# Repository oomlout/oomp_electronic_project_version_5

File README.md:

# OOMP Electronic Projects

**Explore a board, understand its components, and follow it through to manufacturing files.**

This repository brings electronic board projects into a consistent, browsable
collection. Each project keeps its source files, component records, drawings,
and review results together, with interactive explorers and production outputs
where available. Matched parts link back to the
[OOMP Electronics catalogue](https://github.com/oomlout/oomp_electronic_version_5).

**[Browse projects](navigation/README.md)** · **[Board explorer guide](kicad_agents/BOARD_EXPLORER_GUIDE.md)** · **[Add a project](ADDING_PROJECTS.md)** · **[Component catalogue](https://github.com/oomlout/oomp_electronic_version_5)**

[![Component-placement drawing of the Adafruit PWM Servo Shield][board-image]][example]

*Example: [Adafruit PWM Servo Shield][example]. Browse its saved project record
or [open the interactive board explorer][explorer].*

## Find what you need

| I want to… | Start here |
| --- | --- |
| Browse boards and saved versions | [Project catalogue](navigation/README.md) |
| Inspect components, pins, and routed nets | [Board explorer guide](kicad_agents/BOARD_EXPLORER_GUIDE.md) |
| Add another board | [Adding projects](ADDING_PROJECTS.md) and [definition format](project_data/README.md) |
| Understand the converted KiCad design | [Conversion and library guide](kicad_agents/KICAD_LIBRARY_GUIDE.md) |
| Review fabrication and assembly outputs | [Production guide](kicad_agents/PRODUCTION_JLC_GUIDE.md) |
| See where an OOMP component is used | [Component usage](https://oomlout.github.io/oomp_electronic_project_version_5/usage/index.html) |

## What a project contains

- **Saved source files and provenance**, including the upstream board and Git reference.
- **Component matching** against a local OOMP catalogue, with unresolved matches
  and review decisions kept visible.
- **Board drawings and interactive explorers**, plus InteractiveHtmlBom where generated.
- **A separate OOMP KiCad design**, conversion reports, and project-local libraries.
- **Manufacturing outputs where generated**, including Gerbers, assembly files,
  and validation reports for review.

Each project lives in `parts/<project-id>/`. Its page links to the available
files and reports. Custom or modified board items are preserved when they cannot
be replaced with verified library assets.

## Set up a local checkout

Use **Python 3.12 or later**. On Windows, enable Git's long-path support when cloning:

```powershell
git clone -c core.longpaths=true https://github.com/oomlout/oomp_electronic_project_version_5.git C:\gh\oomp_electronic_project_version_5
cd C:\gh\oomp_electronic_project_version_5
py -3.12 -m venv .venv
.\.venv\Scripts\python.exe -m pip install -r requirements.txt
.\.venv\Scripts\Activate.ps1
python action_doctor.py
```

Choose another destination if needed. For an existing checkout, run
`git config core.longpaths true` once. The doctor command reports prerequisites
without changing the checkout.

| Tool | Used for |
| --- | --- |
| KiCad CLI and libraries | Conversion and production output |
| KiCad's Python with `pcbnew` | InteractiveHtmlBom |
| Inkscape | PNG rendering |
| Git | Explicit upstream-source refreshes |

KiCad 10 supports Eagle PCB import, but its CLI does not import an Eagle
schematic/project pair. The existing paired-source refresh path requires a CLI
providing `kicad-cli import`; otherwise it fails explicitly. Use KiCad's
**File → Import Non-KiCad Project** for paired Eagle conversion, then save native
inputs. The migrated native KiCad inputs build without refreshing Eagle sources.

The committed `component_catalog` snapshot supplies component metadata and
assets. Ordinary builds do not access an electronics checkout.
Its compiled matching index contains the same IDs and explicit generic rules as
the saved component records, avoiding thousands of metadata reads per board.

## Build a selected project

Copy its ID from a project page. For example:

```powershell
$projectId = 'oomp_project_github_hanqaqa_easyduino_esp32_current'
python action_generate.py --filter $projectId
```

To explicitly fetch upstream changes and run the production, image, and
interactive BOM stages:

```powershell
python action_generate.py --filter $projectId --refresh-sources --production --images --ibom
```

Normal generation uses saved project inputs. Source refresh is explicit, so a
documentation rebuild cannot silently fetch a different upstream board.
`--regenerate-pngs` replaces preserved PNGs. Missing tools, missing inputs and
failed stages must be resolved before claiming a complete build.

| Task | Command |
| --- | --- |
| Populate definitions without building projects | `python action_generate.py --populate-only` |
| Refresh the component-usage pages | `python action_generate_usage.py` |
| Run the project test suite | `python -m pytest` |
| Check independence from sibling repositories | `python -S tools/run_isolated_tests.py -q` |

### Add a board

Edit `project_data/<owner>/working.yaml`; follow the
[worked example](ADDING_PROJECTS.md) and [definition guide](project_data/README.md).
Project IDs and existing
`parts/<project-id>` paths remain stable. Project records under `parts_source`
are derived from these definitions.
Historical records no longer present in the active definitions remain selectable
by their existing ID and are marked `definition_source: preserved_working_record`.
Their saved Git reference, inputs and review decisions are retained.

## Update the component snapshot

```powershell
python action_sync_component_catalog.py --source C:\gh\oomp_electronic_version_5
```

The default source is configured in [`project_config.json`](project_config.json)
and can point to a different location. It is used only by
the explicit sync command. Updates are copied and checksum-verified in staging,
then installed as a complete snapshot. A previous snapshot is retained at
`component_catalog.previous`; archive it before another update. Inspect the
snapshot manifest and matching changes before committing an update.

Snapshot hashes describe actual imported files. The source commit is recorded
for provenance; local source modifications are not represented by that commit.
Missing component assets are listed explicitly in the manifest.

## Links and publishing

Public repository and Pages addresses are configured in `project_config.json`.
Projects link to canonical component pages. `usage/index.html#<oomp-id>` shows
confirmed project usage and reports incomplete extraction coverage. It also
handles unknown component IDs without requiring a per-component page.

The Pages workflow publishes self-contained board explorers, interactive BOMs and usage pages.
CAD sources, drawings, manufacturing outputs and other downloads are linked from
GitHub. `tools/package_pages.py` checks the publication size before deployment.
Repository settings must use GitHub Actions as the Pages publishing source.

## IC naming

IC component IDs in the frozen catalogue use
`electronic_ic_<function>_<subtype>_<package>_<manufacturer>_<mpn>`.
Function, subtype, and package occupy taxonomy levels **3, 4, and 5**; levels
6–13 are empty and manufacturer/MPN remain at **14/15**. The package is the last
regular taxonomy field. Local `component_taxonomy.package_token` keeps matching
and display code independent of the electronics checkout.

See the [electronics intake guide](https://github.com/oomlout/oomp_electronic_version_5/blob/main/kicad_agents/JLC_PART_INTAKE_AGENT.md)
for adding components under this convention.

## Maintainer reference

[Project tooling](kicad_agents/README.md) · [Adding projects](ADDING_PROJECTS.md) · [Project definitions](project_data/README.md)

<details>
<summary>Repository split and migration history</summary>

### Repository split — 14 November 2026

The split preserved 915 saved projects and imported a dependency snapshot of
2,966 components. Existing drawings, explorers, manufacturing files and review
decisions were moved; no bulk documentation or board regeneration was performed.
Saved reverse usage was relocated without recomputing matches. Twelve projects
were marked as lacking extracted data.

At the split, the isolated project suite passed 92 tests, including native KiCad
conversion and fabrication checks. Four pre-existing assertions remained: the historical
Bus Pirate J302 rotation, IC1 being unmatched despite its saved confirmed match,
an old render zoom, and an old Bus Pirate version expectation. These failures
were checked against the original code/data and retained for separate repair;
the migration does not change board geometry to satisfy them.

### IC naming — 15 November 2026

The catalogue migration moved IC packages after their functional taxonomy and
recomputed MD5/base36/BIP39 codes from canonical IDs. The snapshot manifest
retains its original provenance and records the migration.

</details>

[example]: parts/oomp_project_github_adafruit_adafruit_16_channel_pwm_servo_shield_adafruit_pwm_servo_shield_current/README.md
[board-image]: parts/oomp_project_github_adafruit_adafruit_16_channel_pwm_servo_shield_adafruit_pwm_servo_shield_current/data/generated_data/src/board_300.png
[explorer]: https://oomlout.github.io/oomp_electronic_project_version_5/parts/oomp_project_github_adafruit_adafruit_16_channel_pwm_servo_shield_adafruit_pwm_servo_shield_current/board_explorer.html

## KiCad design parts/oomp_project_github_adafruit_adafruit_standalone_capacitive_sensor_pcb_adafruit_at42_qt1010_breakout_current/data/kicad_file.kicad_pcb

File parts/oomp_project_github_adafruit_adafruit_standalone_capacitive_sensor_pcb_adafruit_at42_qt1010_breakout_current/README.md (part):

# Project adafruit/Adafruit-Standalone-Capacitive-Sensor-PCB Adafruit AT42 QT1010 Breakout current

[View the project on GitHub](https://github.com/adafruit/Adafruit-Standalone-Capacitive-Sensor-PCB/blob/master/Adafruit%20AT42QT1010%20Breakout.brd)

[Open the interactive board explorer (GitHub Pages)](https://oomlout.github.io/oomp_electronic_project_version_5/parts/oomp_project_github_adafruit_adafruit_standalone_capacitive_sensor_pcb_adafruit_at42_qt1010_breakout_current/board_explorer.html)

[Browse this project category](../../navigation/oomp/project/github/adafruit/adafruit_standalone_capacitive_sensor_pcb/adafruit_at42_qt1010_breakout/README.md)

Project adafruit/Adafruit-Standalone-Capacitive-Sensor-PCB Adafruit AT42 QT1010 Breakout current is a KiCad project containing 26 extracted component records. The catalogue matcher linked 9 physical placements to OOMP parts.

## Project snapshot

| Item | Count |
| --- | ---: |
| Components | 26 |
| PCB footprints | 17 |
| Mounting and locating holes | 5 |
| Matched OOMP mounting-hole items | 5 |
| Schematic symbols | 25 |
| Matched OOMP components | 9 |
| Unmatched physical components | 3 |
| Front-side placements | 7 |
| Back-side placements | 1 |
| Project version | `current` |
| Git ref | `master` |

## Board

[Original KiCad files](https://github.com/oomlout/oomp_electronic_project_version_5/tree/main/parts/oomp_project_github_adafruit_adafruit_standalone_capacitive_sensor_pcb_adafruit_at42_qt1010_breakout_current/data/original) · [OOMP KiCad design and local libraries](https://github.com/oomlout/oomp_electronic_project_version_5/tree/main/parts/oomp_project_github_adafruit_adafruit_standalone_capacitive_sensor_pcb_adafruit_at42_qt1010_breakout_current/data/oomp_design) · [Conversion / skipped-item report](https://github.com/oomlout/oomp_electronic_project_version_5/blob/main/parts/oomp_project_github_adafruit_adafruit_standalone_capacitive_sensor_pcb_adafruit_at42_qt1010_breakout_current/data/oomp_design/conversion_report.yaml)

The OOMP design is a separate copy. Only symbols and footprints verified against unchanged installed KiCad masters are replaced; custom and modified items are retained.

- Approximate size: **20.32 mm × 27.94 mm**
- Outline source: `KiCad Edge.Cuts`
- Placement drawing: [view `board.svg`](https://github.com/oomlout/oomp_electronic_project_version_5/blob/main/parts/oomp_project_github_adafruit_adafruit_standalone_capacitive_sensor_pcb_adafruit_at42_qt1010_breakout_current/data/generated_data/src/board.svg)
- PNG placement drawing: [view `board.png`](https://github.com/oomlout/oomp_electronic_project_version_5/blob/main/parts/oomp_project_github_adafruit_adafruit_standalone_capacitive_sensor_pcb_adafruit_at42_qt1010_breakout_current/data/generated_data/src/board.png)
- 300-pixel placement preview: [view `board_300.png`](https://github.com/oomlout/oomp_electronic_project_version_5/blob/main/parts/oomp_project_github_adafruit_adafruit_standalone_capacitive_sensor_pcb_adafruit_at42_qt1010_breakout_current/data/generated_data/src/board_300.png)
- Placement drawing with pin names: [view `board_pins.svg`](https://github.com/oomlout/oomp_electronic_project_version_5/blob/main/parts/oomp_project_github_adafruit_adafruit_standalone_capacitive_sensor_pcb_adafruit_at42_qt1010_breakout_current/data/generated_data/src/board_pins.svg)
- PNG drawing with pin names: [view `board_pins.png`](https://github.com/oomlout/oomp_electronic_project_version_5/blob/main/parts/oomp_project_github_adafruit_adafruit_standalone_capacitive_sensor_pcb_adafruit_at42_qt1010_breakout_current/data/generated_data/src/board_pins.png)
- 300-pixel pin preview: [view `board_pins_300.png`](https://github.com/oomlout/oomp_electronic_project_version_5/blob/main/parts/oomp_project_github_adafruit_adafruit_standalone_capacitive_sensor_pcb_adafruit_at42_qt1010_breakout_current/data/generated_data/src/board_pins_300.png)
- Bottom placement drawing: [view `board_bottom.svg`](https://github.com/oomlout/oomp_electronic_project_version_5/blob/main/parts/oomp_project_github_adafruit_adafruit_standalone_capacitive_sensor_pcb_adafruit_at42_qt1010_breakout_current/data/generated_data/src/board_bottom.svg)
- Bottom PNG placement drawing: [view `board_bottom.png`](https://github.com/oomlout/oomp_electronic_project_version_5/blob/main/parts/oomp_project_github_adafruit_adafruit_standalone_capacitive_sensor_pcb_adafruit_at42_qt1010_breakout_current/data/generated_data/src/board_bottom.png)
- 300-pixel bottom preview: [view `board_bottom_300.png`](https://github.com/oomlout/oomp_electronic_project_version_5/blob/main/parts/oomp_project_github_adafruit_adafruit_standalone_capacitive_sensor_pcb_adafruit_at42_qt1010_breakout_current/data/generated_data/src/board_bottom_300.png)
- Bottom placement drawing with pin names: [view `board_pins_bottom.svg`](https://github.com/oomlout/oomp_electronic_project_version_5/blob/main/parts/oomp_project_github_adafruit_adafruit_standalone_capacitive_sensor_pcb_adafruit_at42_qt1010_breakout_current/data/generated_data/src/board_pins_bottom.svg)
- Bottom PNG drawing with pin names: [view `board_pins_bottom.png`](https://github.com/oomlout/oomp_electronic_project_version_5/blob/main/parts/oomp_project_github_adafruit_adafruit_standalone_capacitive_sensor_pcb_adafruit_at42_qt1010_breakout_current/data/generated_data/src/board_pins_bottom.png)
- 300-pixel bottom pin preview: [view `board_pins_bottom_300.png`](https://github.com/oomlout/oomp_electronic_project_version_5/blob/main/parts/oomp_project_github_adafruit_adafruit_standalone_capacitive_sensor_pcb_adafruit_at42_qt1010_breakout_current/data/generated_data/src/board_pins_bottom_300.png)
- Mechanical drawing: [view `board_mechanical.svg`](https://github.com/oomlout/oomp_electronic_project_version_5/blob/main/parts/oomp_project_github_adafruit_adafruit_standalone_capacitive_sensor_pcb_adafruit_at42_qt1010_breakout_current/data/generated_data/src/board_mechanical.svg)
- Mechanical PNG: [view `board_mechanical.png`](https://github.com/oomlout/oomp_electronic_project_version_5/blob/main/parts/oomp_project_github_adafruit_adafruit_standalone_capacitive_sensor_pcb_adafruit_at42_qt1010_breakout_current/data/generated_data/src/board_mechanical.png)
- 300-pixel mechanical preview: [view `board_mechanical_300.png`](https://github.com/oomlout/oomp_electronic_project_version_5/blob/main/parts/oomp_project_github_adafruit_adafruit_standalone_capacitive_sensor_pcb_adafruit_at42_qt1010_breakout_current/data/generated_data/src/board_mechanical_300.png)
- Open the board explorer on GitHub Pages: [explore this board](https://oomlout.github.io/oomp_electronic_project_version_5/parts/oomp_project_github_adafruit_adafruit_standalone_capacitive_sensor_pcb_adafruit_at42_qt1010_breakout_current/board_explorer.html)
- InteractiveHtmlBom generation is configured; install KiCad or set `KICAD_PYTHON` to its bundled Python to build `data/interactivehtmlbom/ibom.html`.

## Board with pins

## Bottom board with pins

The bottom view is mirrored horizontally so it is shown as viewed from beneath the assembled board.

## Mechanical layer

The table uses a board-relative origin at the minimum X/Y point of `Edge.Cuts`. This point is shown as **0,0** in the mechanical drawing; X increases right and Y increases down. Original KiCad coordinates are retained alongside it.

### Diameter 2.5 mm holes

| OOMP reference | Source | Name | Classification | Role | Board X (mm) | Board Y (mm) | OOMP part |
| --- | --- | --- | --- | --- | ---: | ---: | --- |
| `MH1` | `LED1` | Mounting Hole 2.5 mm Round Unplated | `mechanical / mounting_hole / 2_5_mm / round / unplated` | locating | 10.230 | 2.183 | [`mechanical_mounting_hole_2_5_mm_round_unplated`](https://github.com/oomlout/oomp_electronic_version_5/tree/main/parts/mechanical_mounting_hole_2_5_mm_round_unplated) |
| `MH2` | `U$6` | Mounting Hole 2.5 mm Round Plated | `mechanical / mounting_hole / 2_5_mm / round / plated` | mounting | 17.780 | 25.400 | [`mechanical_mounting_hole_2_5_mm_round_plated`](https://github.com/oomlout/oomp_electronic_version_5/tree/main/parts/mechanical_mounting_hole_2_5_mm_round_plated) |
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
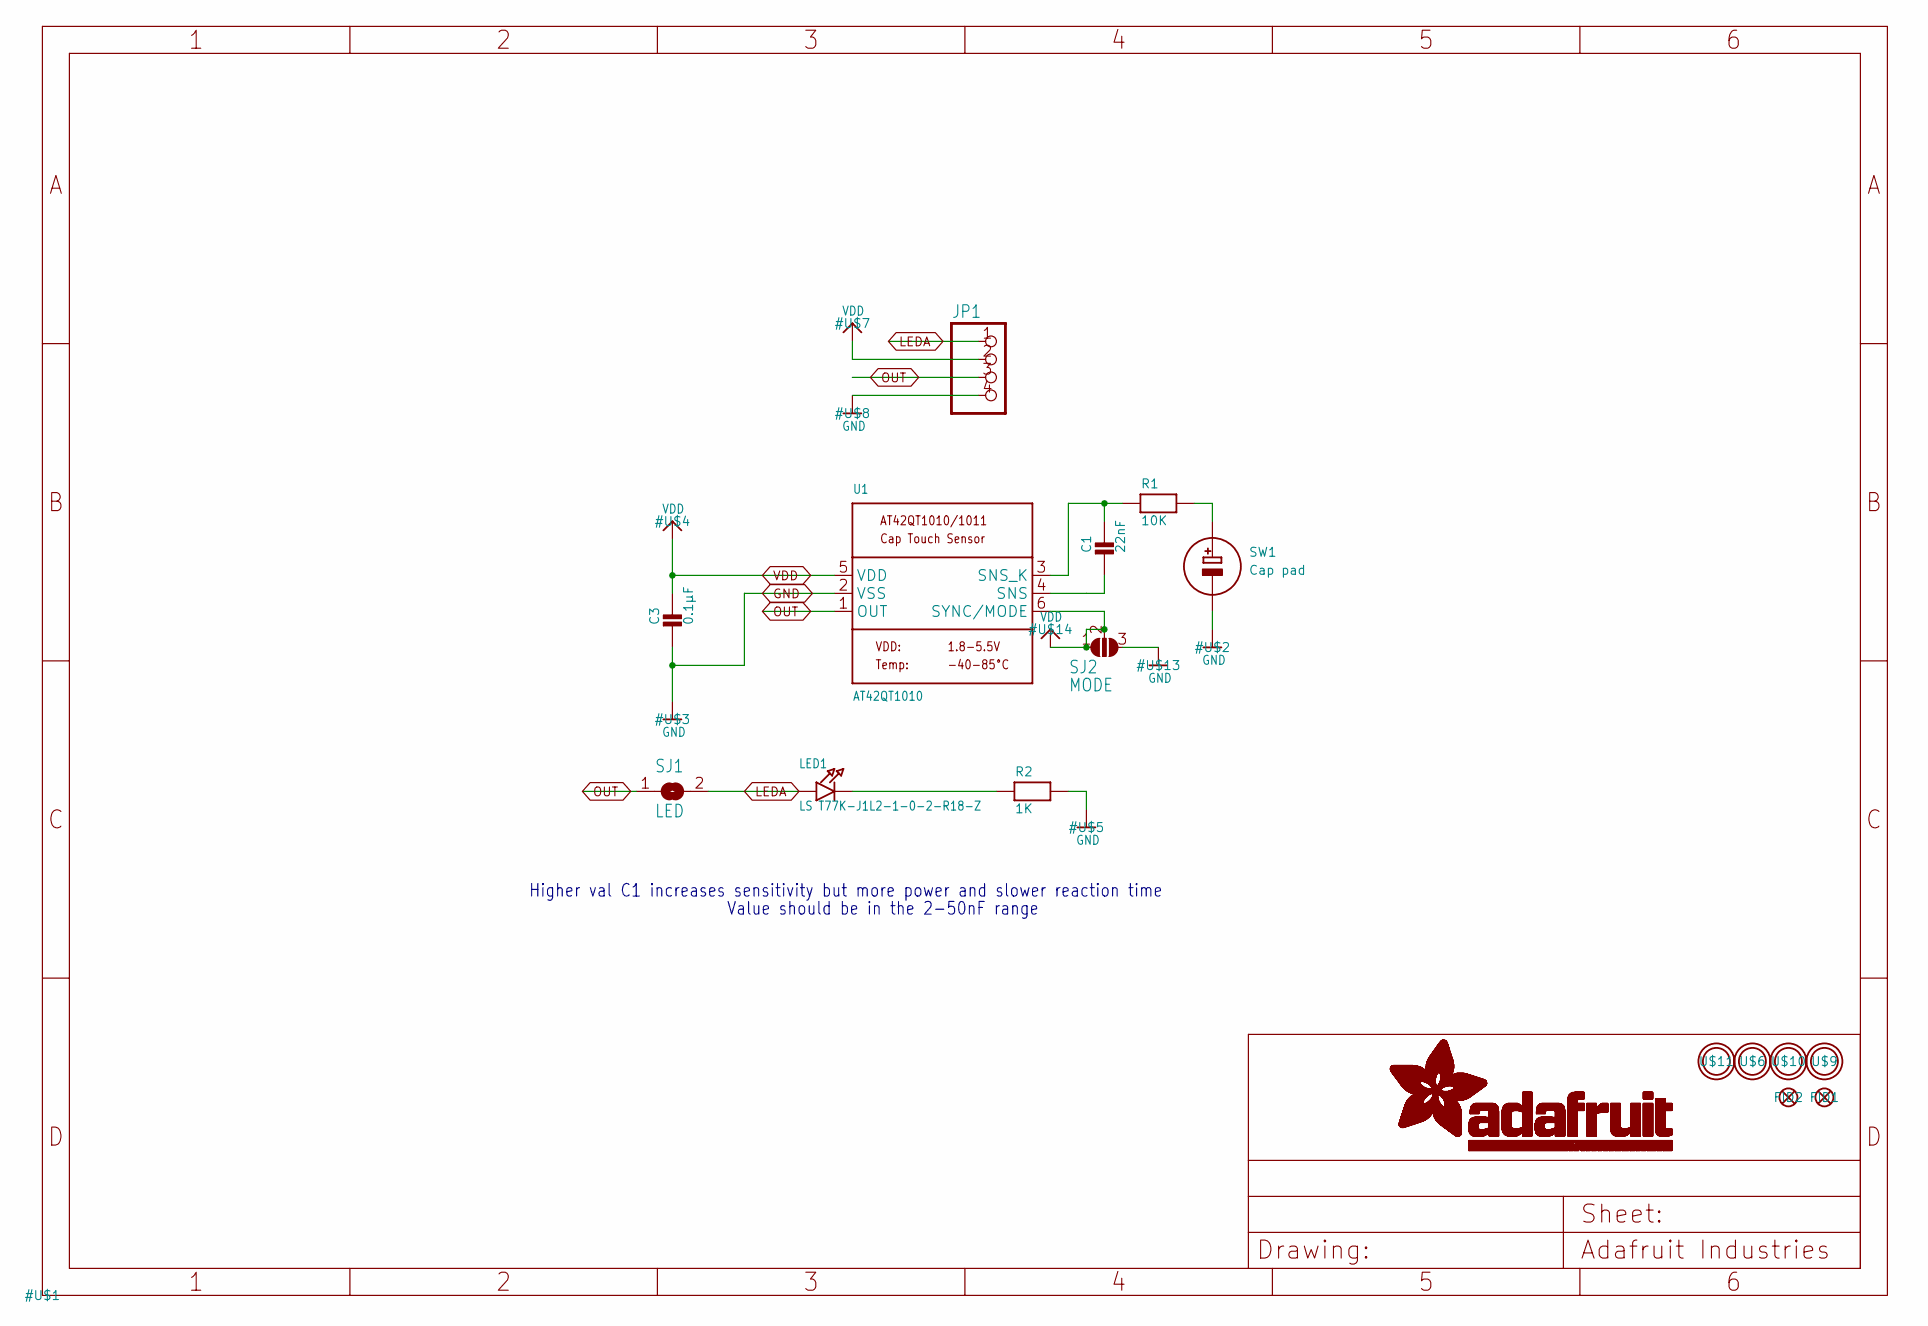
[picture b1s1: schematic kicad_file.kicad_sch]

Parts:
C1: 22nF; _0805
C3: 0.1µF; _0805
FID1, FID2: FIDUCIAL""; FIDUCIAL_1MM
JP1: HEADER-1X476MIL; 1X04_ROUND_76
LED1: LS T77K-J1L2-1-0-2-R18-Z; PLCC2_REVMOUNT
R1: 10K; _0805
R2: 1K; _0805
SJ1: LED; SOLDERJUMPER_CLOSEDWIRE
SJ2: MODE; SOLDERJUMPER_2WAY_OPEN_NOPASTE
SW1: Cap pad; CAPTOUCH_SIMPLE_12.5MM
U1: AT42QT1010; SOT23-6
U$6, U$9, U$10, U$11: MOUNTINGHOLE2.5; MOUNTINGHOLE_2.5_PLATED

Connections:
CAPPAD: R1.2, SW1.E (+)
GND: C3.2, JP1.4, R2.2, SJ2.3, SW1.G (-), U1.2 (VSS)
LEDA: JP1.1, LED1.A, SJ1.2
unnamed: C1.2, U1.4 (SNS)
unnamed: C1.1, R1.1, U1.3 (SNS_K)
unnamed: LED1.K (C), R2.1
OUT: JP1.3, SJ1.1, U1.1 (OUT)
VDD: C3.1, JP1.2, SJ2.1, SJ2.2, U1.5 (VDD), U1.6 (SYNC/MODE)

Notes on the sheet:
Value should be in the 2-50nF range
Higher val C1 increases sensitivity but more power and slower reaction time

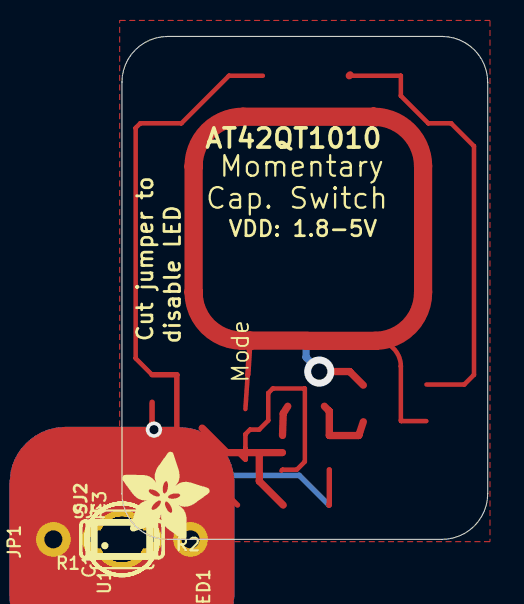
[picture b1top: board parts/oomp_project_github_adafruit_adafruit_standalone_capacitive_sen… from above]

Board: 2 copper layers, 20.3 x 27.9 mm, 17 parts (1 on the bottom side), 8 nets.

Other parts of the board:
U$12: ADAFRUIT_5MM

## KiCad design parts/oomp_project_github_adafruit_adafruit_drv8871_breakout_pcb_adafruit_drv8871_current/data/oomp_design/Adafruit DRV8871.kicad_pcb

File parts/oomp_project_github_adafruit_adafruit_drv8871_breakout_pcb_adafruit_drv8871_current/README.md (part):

# Project adafruit/Adafruit-DRV8871-Breakout-PCB Adafruit DRV8871 current

[View the project on GitHub](https://github.com/adafruit/Adafruit-DRV8871-Breakout-PCB/blob/master/Adafruit%20DRV8871.brd)

[Open the interactive board explorer (GitHub Pages)](https://oomlout.github.io/oomp_electronic_project_version_5/parts/oomp_project_github_adafruit_adafruit_drv8871_breakout_pcb_adafruit_drv8871_current/board_explorer.html)

[Browse this project category](../../navigation/oomp/project/github/adafruit/adafruit_drv8871_breakout_pcb/adafruit_drv8871/README.md)

Project adafruit/Adafruit-DRV8871-Breakout-PCB Adafruit DRV8871 current is a KiCad project containing 26 extracted component records. The catalogue matcher linked 5 physical placements to OOMP parts.

## Project snapshot

| Item | Count |
| --- | ---: |
| Components | 26 |
| PCB footprints | 15 |
| Mounting and locating holes | 6 |
| Matched OOMP mounting-hole items | 2 |
| Schematic symbols | 23 |
| Matched OOMP components | 5 |
| Unmatched physical components | 4 |
| Front-side placements | 7 |
| Back-side placements | 0 |
| Project version | `current` |
| Git ref | `master` |

## Board

[Original KiCad files](https://github.com/oomlout/oomp_electronic_project_version_5/tree/main/parts/oomp_project_github_adafruit_adafruit_drv8871_breakout_pcb_adafruit_drv8871_current/data/original) · [OOMP KiCad design and local libraries](https://github.com/oomlout/oomp_electronic_project_version_5/tree/main/parts/oomp_project_github_adafruit_adafruit_drv8871_breakout_pcb_adafruit_drv8871_current/data/oomp_design) · [Conversion / skipped-item report](https://github.com/oomlout/oomp_electronic_project_version_5/blob/main/parts/oomp_project_github_adafruit_adafruit_drv8871_breakout_pcb_adafruit_drv8871_current/data/oomp_design/conversion_report.yaml)

The OOMP design is a separate copy. Only symbols and footprints verified against unchanged installed KiCad masters are replaced; custom and modified items are retained.

- Approximate size: **20.32 mm × 24.13 mm**
- Outline source: `KiCad Edge.Cuts`
- Placement drawing: [view `board.svg`](https://github.com/oomlout/oomp_electronic_project_version_5/blob/main/parts/oomp_project_github_adafruit_adafruit_drv8871_breakout_pcb_adafruit_drv8871_current/data/generated_data/src/board.svg)
- PNG placement drawing: [view `board.png`](https://github.com/oomlout/oomp_electronic_project_version_5/blob/main/parts/oomp_project_github_adafruit_adafruit_drv8871_breakout_pcb_adafruit_drv8871_current/data/generated_data/src/board.png)
- 300-pixel placement preview: [view `board_300.png`](https://github.com/oomlout/oomp_electronic_project_version_5/blob/main/parts/oomp_project_github_adafruit_adafruit_drv8871_breakout_pcb_adafruit_drv8871_current/data/generated_data/src/board_300.png)
- Placement drawing with pin names: [view `board_pins.svg`](https://github.com/oomlout/oomp_electronic_project_version_5/blob/main/parts/oomp_project_github_adafruit_adafruit_drv8871_breakout_pcb_adafruit_drv8871_current/data/generated_data/src/board_pins.svg)
- PNG drawing with pin names: [view `board_pins.png`](https://github.com/oomlout/oomp_electronic_project_version_5/blob/main/parts/oomp_project_github_adafruit_adafruit_drv8871_breakout_pcb_adafruit_drv8871_current/data/generated_data/src/board_pins.png)
- 300-pixel pin preview: [view `board_pins_300.png`](https://github.com/oomlout/oomp_electronic_project_version_5/blob/main/parts/oomp_project_github_adafruit_adafruit_drv8871_breakout_pcb_adafruit_drv8871_current/data/generated_data/src/board_pins_300.png)
- Bottom placement drawing: [view `board_bottom.svg`](https://github.com/oomlout/oomp_electronic_project_version_5/blob/main/parts/oomp_project_github_adafruit_adafruit_drv8871_breakout_pcb_adafruit_drv8871_current/data/generated_data/src/board_bottom.svg)
- Bottom PNG placement drawing: [view `board_bottom.png`](https://github.com/oomlout/oomp_electronic_project_version_5/blob/main/parts/oomp_project_github_adafruit_adafruit_drv8871_breakout_pcb_adafruit_drv8871_current/data/generated_data/src/board_bottom.png)
- 300-pixel bottom preview: [view `board_bottom_300.png`](https://github.com/oomlout/oomp_electronic_project_version_5/blob/main/parts/oomp_project_github_adafruit_adafruit_drv8871_breakout_pcb_adafruit_drv8871_current/data/generated_data/src/board_bottom_300.png)
- Bottom placement drawing with pin names: [view `board_pins_bottom.svg`](https://github.com/oomlout/oomp_electronic_project_version_5/blob/main/parts/oomp_project_github_adafruit_adafruit_drv8871_breakout_pcb_adafruit_drv8871_current/data/generated_data/src/board_pins_bottom.svg)
- Bottom PNG drawing with pin names: [view `board_pins_bottom.png`](https://github.com/oomlout/oomp_electronic_project_version_5/blob/main/parts/oomp_project_github_adafruit_adafruit_drv8871_breakout_pcb_adafruit_drv8871_current/data/generated_data/src/board_pins_bottom.png)
- 300-pixel bottom pin preview: [view `board_pins_bottom_300.png`](https://github.com/oomlout/oomp_electronic_project_version_5/blob/main/parts/oomp_project_github_adafruit_adafruit_drv8871_breakout_pcb_adafruit_drv8871_current/data/generated_data/src/board_pins_bottom_300.png)
- Mechanical drawing: [view `board_mechanical.svg`](https://github.com/oomlout/oomp_electronic_project_version_5/blob/main/parts/oomp_project_github_adafruit_adafruit_drv8871_breakout_pcb_adafruit_drv8871_current/data/generated_data/src/board_mechanical.svg)
- Mechanical PNG: [view `board_mechanical.png`](https://github.com/oomlout/oomp_electronic_project_version_5/blob/main/parts/oomp_project_github_adafruit_adafruit_drv8871_breakout_pcb_adafruit_drv8871_current/data/generated_data/src/board_mechanical.png)
- 300-pixel mechanical preview: [view `board_mechanical_300.png`](https://github.com/oomlout/oomp_electronic_project_version_5/blob/main/parts/oomp_project_github_adafruit_adafruit_drv8871_breakout_pcb_adafruit_drv8871_current/data/generated_data/src/board_mechanical_300.png)
- Open the board explorer on GitHub Pages: [explore this board](https://oomlout.github.io/oomp_electronic_project_version_5/parts/oomp_project_github_adafruit_adafruit_drv8871_breakout_pcb_adafruit_drv8871_current/board_explorer.html)
- InteractiveHtmlBom generation is configured; install KiCad or set `KICAD_PYTHON` to its bundled Python to build `data/interactivehtmlbom/ibom.html`.

## Board with pins

## Bottom board with pins

The bottom view is mirrored horizontally so it is shown as viewed from beneath the assembled board.

## Mechanical layer

The table uses a board-relative origin at the minimum X/Y point of `Edge.Cuts`. This point is shown as **0,0** in the mechanical drawing; X increases right and Y increases down. Original KiCad coordinates are retained alongside it.

### Diameter 0.4 mm holes

| OOMP reference | Source | Name | Classification | Role | Board X (mm) | Board Y (mm) | OOMP part |
| --- | --- | --- | --- | --- | ---: | ---: | --- |
| `MH1` | `U1` | Mounting Hole 0.4 mm Round Plated | `` | shield_mount | 3.699 | 12.458 | unmatched (`mechanical_mounting_hole_0_4_mm_round_plated` proposed) |
| `MH2` | `U1` | Mounting Hole 0.4 mm Round Plated | `` | shield_mount | 3.699 | 13.958 | unmatched (`mechanical_mounting_hole_0_4_mm_round_plated` proposed) |
| `MH4` | `U1` | Mounting Hole 0.4 mm Round Plated | `` | shield_mount | 5.699 | 12.458 | unmatched (`mechanical_mounting_hole_0_4_mm_round_plated` proposed) |
| `MH3` | `U1` | Mounting Hole 0.4 mm Round Plated | `` | shield_mount | 5.699 | 13.958 | unmatched (`mechanical_mounting_hole_0_4_mm_round_plated` proposed) |

### Diameter 2.5 mm holes

| OOMP reference | Source | Name | Classification | Role | Board X (mm) | Board Y (mm) | OOMP part |
| --- | --- | --- | --- | --- | ---: | ---: | --- |
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
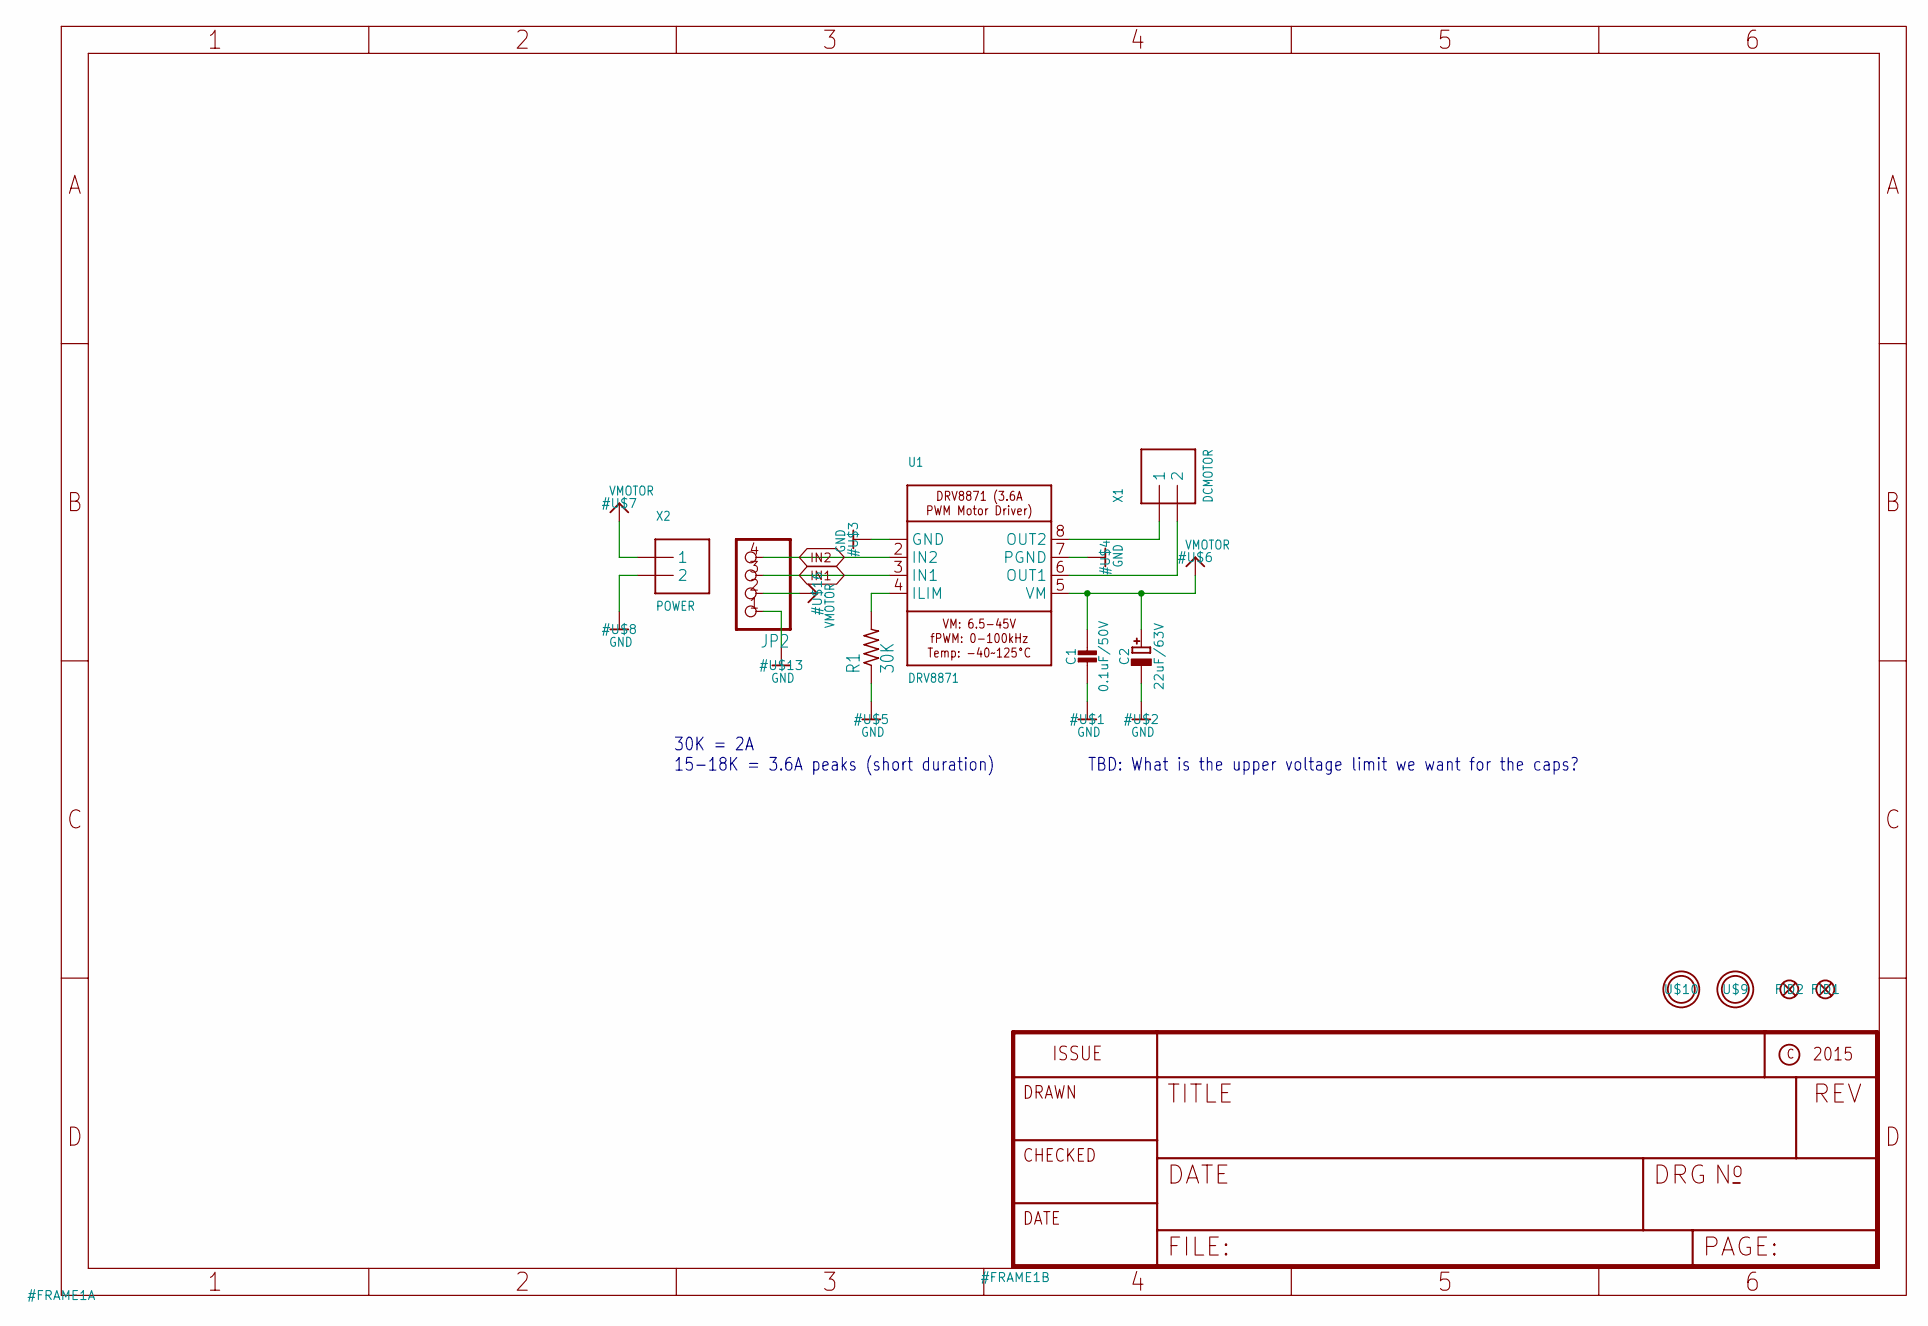
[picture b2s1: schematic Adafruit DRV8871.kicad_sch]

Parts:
C1: 0.1uF/50V; 0805-NO
C2: 22uF/63V; PANASONIC_D
FID1, FID2: FIDUCIAL""; FIDUCIAL_1MM
JP2: HEADER-1X476MIL; 1X04_ROUND_76
R1: 30K; 0805-THM
U1: DRV8871; HSOP8
U$9, U$10: MOUNTINGHOLE2.5; MOUNTINGHOLE_2.5_PLATED
X1: DCMOTOR; TERMBLOCK_1X2-3.5MM
X2: POWER; TERMBLOCK_1X2-3.5MM

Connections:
GND: C1.2, C2.-, JP2.1, R1.1, U1.1 (GND), U1.7 (PGND), U1.GND, U1.P$1 (GND), U1.P$2 (GND), U1.P$3 (GND), U1.P$4 (GND), X2.2
IN1: JP2.3, U1.3 (IN1)
IN2: JP2.4, U1.2 (IN2)
unnamed: R1.2, U1.4 (ILIM)
OUT1: U1.6 (OUT1), X1.2
OUT2: U1.8 (OUT2), X1.1
VMOTOR: C1.1, C2.+, JP2.2, U1.5 (VM), X2.1

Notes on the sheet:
30K = 2A 15-18K = 3.6A peaks (short duration~{})
TBD: What is the upper voltage limit we want for the caps?

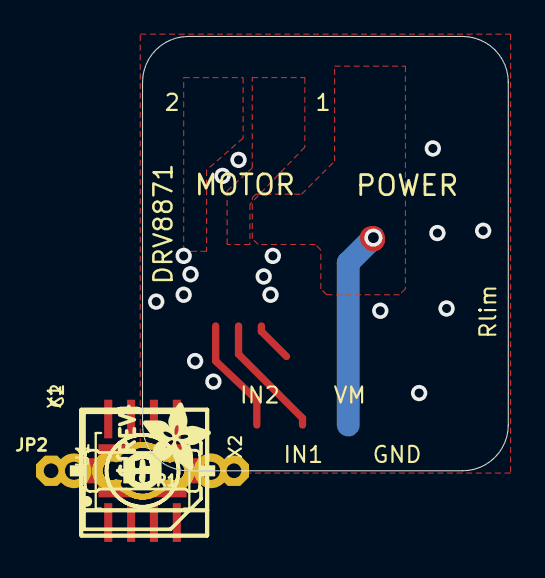
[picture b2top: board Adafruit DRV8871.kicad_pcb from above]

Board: 2 copper layers, 20.3 x 24.1 mm, 15 parts (0 on the bottom side), 7 nets.

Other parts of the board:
U$11: SYMBOL_PLUS
U$12: SYMBOL_MINUS
U$14: ADAFRUIT_3.5MM
U$15: PCBFEAT-REV-040

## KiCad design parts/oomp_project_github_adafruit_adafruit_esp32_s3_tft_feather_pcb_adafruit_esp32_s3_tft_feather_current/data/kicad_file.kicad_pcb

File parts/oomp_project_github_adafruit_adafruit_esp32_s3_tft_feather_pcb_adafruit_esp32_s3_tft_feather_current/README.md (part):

# Project adafruit/Adafruit-ESP32-S3-TFT-Feather-PCB Adafruit ESP32 S3 TFT Feather current

[View the project on GitHub](https://github.com/adafruit/Adafruit-ESP32-S3-TFT-Feather-PCB/blob/main/Adafruit%20ESP32-S3%20TFT%20Feather.brd)

[Open the interactive board explorer (GitHub Pages)](https://oomlout.github.io/oomp_electronic_project_version_5/parts/oomp_project_github_adafruit_adafruit_esp32_s3_tft_feather_pcb_adafruit_esp32_s3_tft_feather_current/board_explorer.html)

[Browse this project category](../../navigation/oomp/project/github/adafruit/adafruit_esp32_s3_tft_feather_pcb/adafruit_esp32_s3_tft_feather/README.md)

Project adafruit/Adafruit-ESP32-S3-TFT-Feather-PCB Adafruit ESP32 S3 TFT Feather current is a KiCad project containing 112 extracted component records. The catalogue matcher linked 32 physical placements to OOMP parts.

## Project snapshot

| Item | Count |
| --- | ---: |
| Components | 112 |
| PCB footprints | 56 |
| Mounting and locating holes | 8 |
| Matched OOMP mounting-hole items | 8 |
| Schematic symbols | 115 |
| Matched OOMP components | 32 |
| Unmatched physical components | 16 |
| Front-side placements | 33 |
| Back-side placements | 11 |
| Project version | `current` |
| Git ref | `main` |

## Board

[Original KiCad files](https://github.com/oomlout/oomp_electronic_project_version_5/tree/main/parts/oomp_project_github_adafruit_adafruit_esp32_s3_tft_feather_pcb_adafruit_esp32_s3_tft_feather_current/data/original) · [OOMP KiCad design and local libraries](https://github.com/oomlout/oomp_electronic_project_version_5/tree/main/parts/oomp_project_github_adafruit_adafruit_esp32_s3_tft_feather_pcb_adafruit_esp32_s3_tft_feather_current/data/oomp_design) · [Conversion / skipped-item report](https://github.com/oomlout/oomp_electronic_project_version_5/blob/main/parts/oomp_project_github_adafruit_adafruit_esp32_s3_tft_feather_pcb_adafruit_esp32_s3_tft_feather_current/data/oomp_design/conversion_report.yaml)

The OOMP design is a separate copy. Only symbols and footprints verified against unchanged installed KiCad masters are replaced; custom and modified items are retained.

- Approximate size: **50.8 mm × 22.86 mm**
- Outline source: `KiCad Edge.Cuts`
- Placement drawing: [view `board.svg`](https://github.com/oomlout/oomp_electronic_project_version_5/blob/main/parts/oomp_project_github_adafruit_adafruit_esp32_s3_tft_feather_pcb_adafruit_esp32_s3_tft_feather_current/data/generated_data/src/board.svg)
- PNG placement drawing: [view `board.png`](https://github.com/oomlout/oomp_electronic_project_version_5/blob/main/parts/oomp_project_github_adafruit_adafruit_esp32_s3_tft_feather_pcb_adafruit_esp32_s3_tft_feather_current/data/generated_data/src/board.png)
- 300-pixel placement preview: [view `board_300.png`](https://github.com/oomlout/oomp_electronic_project_version_5/blob/main/parts/oomp_project_github_adafruit_adafruit_esp32_s3_tft_feather_pcb_adafruit_esp32_s3_tft_feather_current/data/generated_data/src/board_300.png)
- Placement drawing with pin names: [view `board_pins.svg`](https://github.com/oomlout/oomp_electronic_project_version_5/blob/main/parts/oomp_project_github_adafruit_adafruit_esp32_s3_tft_feather_pcb_adafruit_esp32_s3_tft_feather_current/data/generated_data/src/board_pins.svg)
- PNG drawing with pin names: [view `board_pins.png`](https://github.com/oomlout/oomp_electronic_project_version_5/blob/main/parts/oomp_project_github_adafruit_adafruit_esp32_s3_tft_feather_pcb_adafruit_esp32_s3_tft_feather_current/data/generated_data/src/board_pins.png)
- 300-pixel pin preview: [view `board_pins_300.png`](https://github.com/oomlout/oomp_electronic_project_version_5/blob/main/parts/oomp_project_github_adafruit_adafruit_esp32_s3_tft_feather_pcb_adafruit_esp32_s3_tft_feather_current/data/generated_data/src/board_pins_300.png)
- Bottom placement drawing: [view `board_bottom.svg`](https://github.com/oomlout/oomp_electronic_project_version_5/blob/main/parts/oomp_project_github_adafruit_adafruit_esp32_s3_tft_feather_pcb_adafruit_esp32_s3_tft_feather_current/data/generated_data/src/board_bottom.svg)
- Bottom PNG placement drawing: [view `board_bottom.png`](https://github.com/oomlout/oomp_electronic_project_version_5/blob/main/parts/oomp_project_github_adafruit_adafruit_esp32_s3_tft_feather_pcb_adafruit_esp32_s3_tft_feather_current/data/generated_data/src/board_bottom.png)
- 300-pixel bottom preview: [view `board_bottom_300.png`](https://github.com/oomlout/oomp_electronic_project_version_5/blob/main/parts/oomp_project_github_adafruit_adafruit_esp32_s3_tft_feather_pcb_adafruit_esp32_s3_tft_feather_current/data/generated_data/src/board_bottom_300.png)
- Bottom placement drawing with pin names: [view `board_pins_bottom.svg`](https://github.com/oomlout/oomp_electronic_project_version_5/blob/main/parts/oomp_project_github_adafruit_adafruit_esp32_s3_tft_feather_pcb_adafruit_esp32_s3_tft_feather_current/data/generated_data/src/board_pins_bottom.svg)
- Bottom PNG drawing with pin names: [view `board_pins_bottom.png`](https://github.com/oomlout/oomp_electronic_project_version_5/blob/main/parts/oomp_project_github_adafruit_adafruit_esp32_s3_tft_feather_pcb_adafruit_esp32_s3_tft_feather_current/data/generated_data/src/board_pins_bottom.png)
- 300-pixel bottom pin preview: [view `board_pins_bottom_300.png`](https://github.com/oomlout/oomp_electronic_project_version_5/blob/main/parts/oomp_project_github_adafruit_adafruit_esp32_s3_tft_feather_pcb_adafruit_esp32_s3_tft_feather_current/data/generated_data/src/board_pins_bottom_300.png)
- Mechanical drawing: [view `board_mechanical.svg`](https://github.com/oomlout/oomp_electronic_project_version_5/blob/main/parts/oomp_project_github_adafruit_adafruit_esp32_s3_tft_feather_pcb_adafruit_esp32_s3_tft_feather_current/data/generated_data/src/board_mechanical.svg)
- Mechanical PNG: [view `board_mechanical.png`](https://github.com/oomlout/oomp_electronic_project_version_5/blob/main/parts/oomp_project_github_adafruit_adafruit_esp32_s3_tft_feather_pcb_adafruit_esp32_s3_tft_feather_current/data/generated_data/src/board_mechanical.png)
- 300-pixel mechanical preview: [view `board_mechanical_300.png`](https://github.com/oomlout/oomp_electronic_project_version_5/blob/main/parts/oomp_project_github_adafruit_adafruit_esp32_s3_tft_feather_pcb_adafruit_esp32_s3_tft_feather_current/data/generated_data/src/board_mechanical_300.png)
- Open the board explorer on GitHub Pages: [explore this board](https://oomlout.github.io/oomp_electronic_project_version_5/parts/oomp_project_github_adafruit_adafruit_esp32_s3_tft_feather_pcb_adafruit_esp32_s3_tft_feather_current/board_explorer.html)
- InteractiveHtmlBom generation is configured; install KiCad or set `KICAD_PYTHON` to its bundled Python to build `data/interactivehtmlbom/ibom.html`.

## Board with pins

## Bottom board with pins

The bottom view is mirrored horizontally so it is shown as viewed from beneath the assembled board.

## Mechanical layer

The table uses a board-relative origin at the minimum X/Y point of `Edge.Cuts`. This point is shown as **0,0** in the mechanical drawing; X increases right and Y increases down. Original KiCad coordinates are retained alongside it.

### Diameter 1 mm holes

| OOMP reference | Source | Name | Classification | Role | Board X (mm) | Board Y (mm) | OOMP part |
| --- | --- | --- | --- | --- | ---: | ---: | --- |
| `MH2` | `DISP1` | Mounting Hole 1 mm Round Unplated | `mechanical / mounting_hole / 1_mm / round / unplated` | locating | 14.118 | 6.170 | [`mechanical_mounting_hole_1_mm_round_unplated`](https://github.com/oomlout/oomp_electronic_version_5/tree/main/parts/mechanical_mounting_hole_1_mm_round_unplated) |
| `MH1` | `DISP1` | Mounting Hole 1 mm Round Unplated | `mechanical / mounting_hole / 1_mm / round / unplated` | locating | 14.118 | 16.570 | [`mechanical_mounting_hole_1_mm_round_unplated`](https://github.com/oomlout/oomp_electronic_version_5/tree/main/parts/mechanical_mounting_hole_1_mm_round_unplated) |

### Diameter 2.5 mm holes

| OOMP reference | Source | Name | Classification | Role | Board X (mm) | Board Y (mm) | OOMP part |
| --- | --- | --- | --- | --- | ---: | ---: | --- |
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
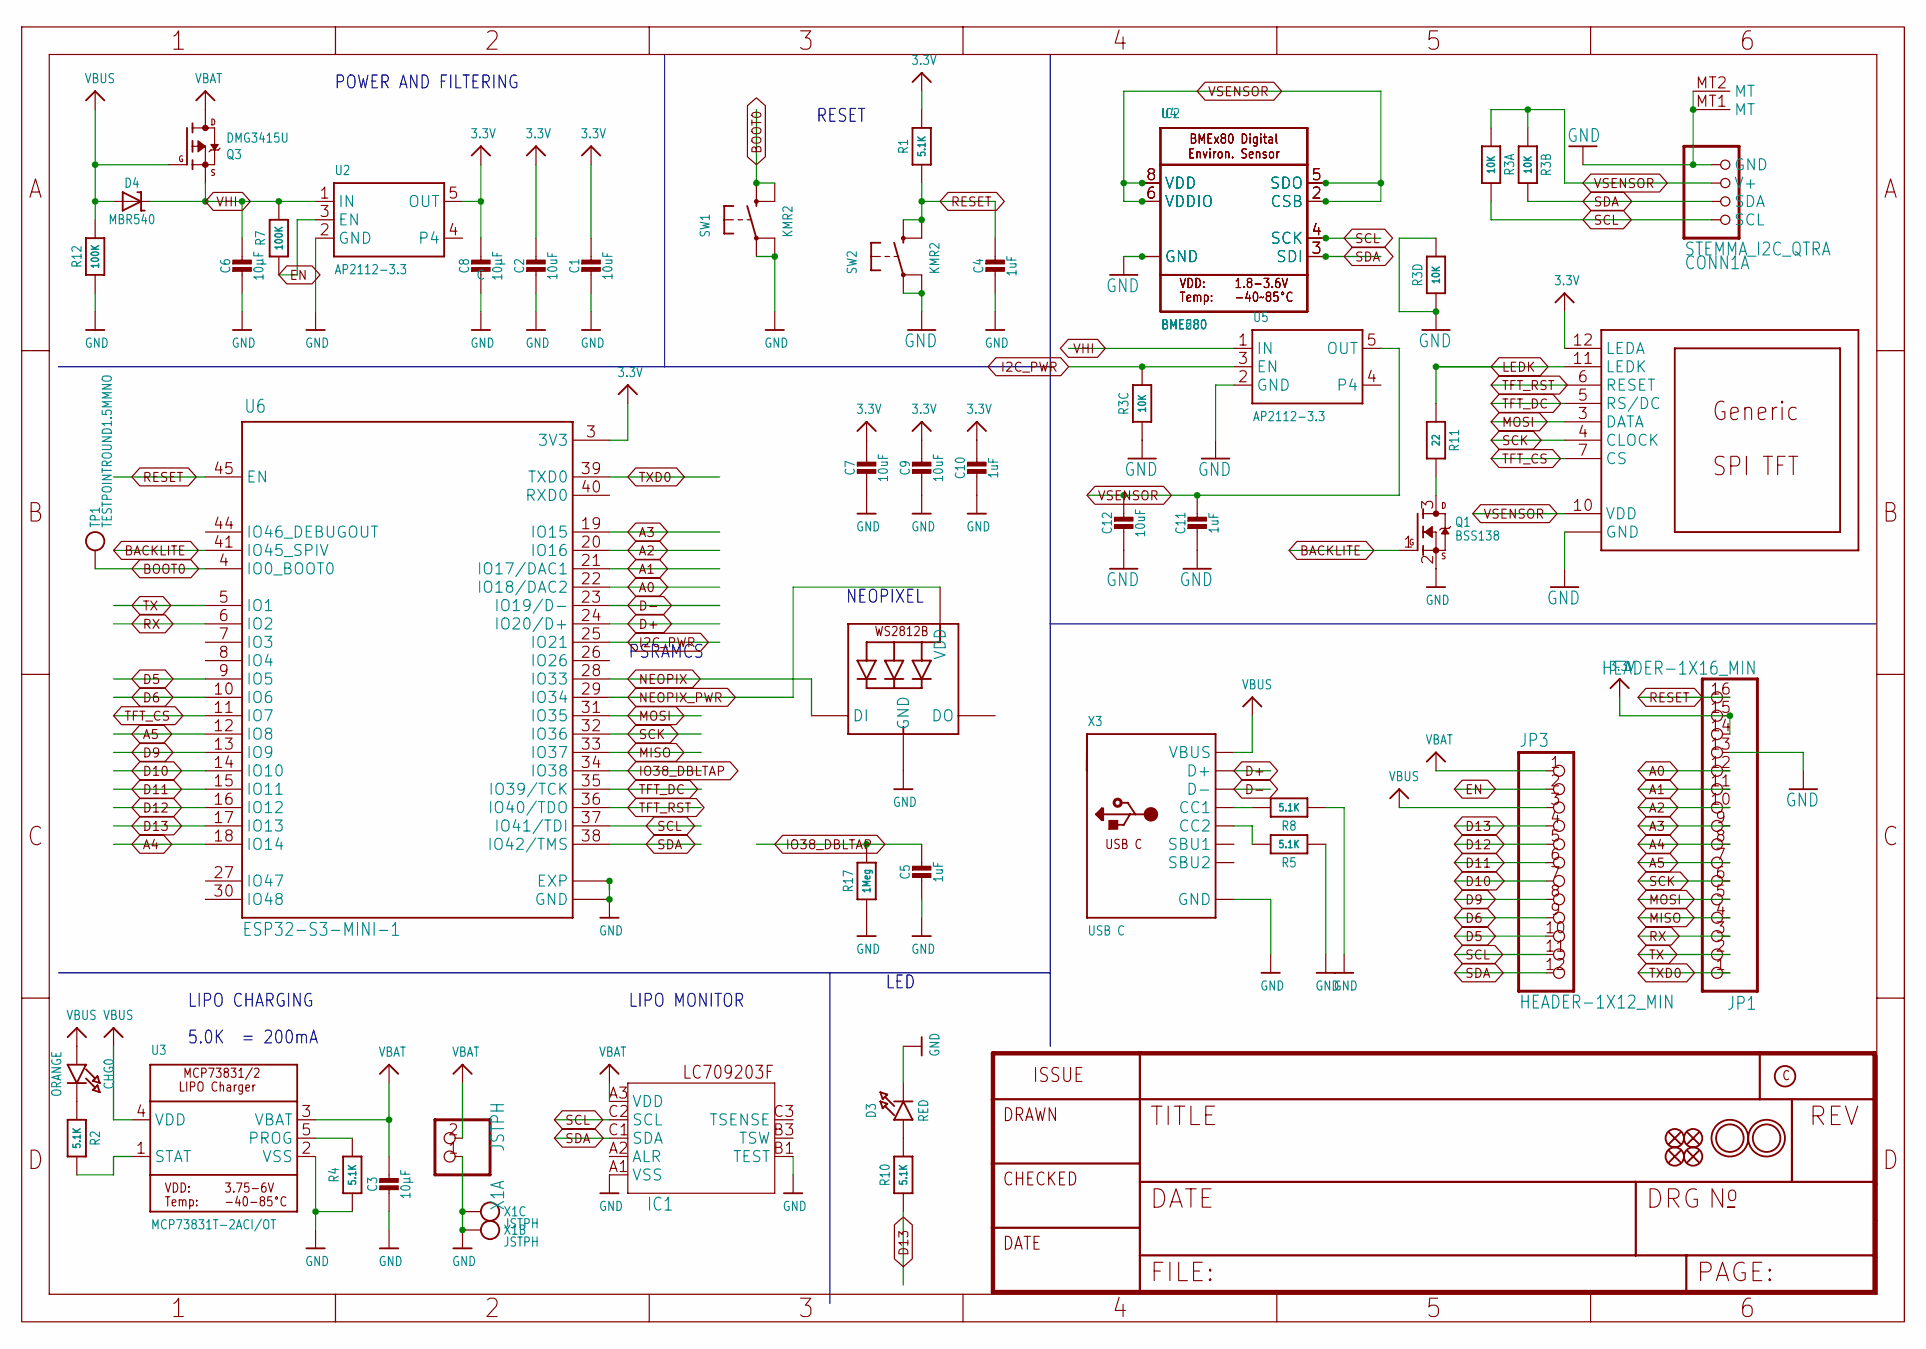
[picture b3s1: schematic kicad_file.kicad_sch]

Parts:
C1, C2, C7, C9, C12: 10uF; 0805-NO
C3, C6, C8: 10µF; 0805-NO
C4, C5, C10, C11: 1uF; 0603-NO
CHG0: ORANGE; CHIPLED_0603_NOOUTLINE
CONN1: STEMMA_I2C_QTRA; JST_SH4_RA
D3: RED; CHIPLED_0603_NOOUTLINE
D4: MBR540; SOD-123
DISP1: DISP_LCD_GENERIC_SPI_1.14IN_240X135_WRAPUNDER; TFT_1.14IN_240X135_WRAPUNDER
IC1: LC709203F/MH; WLCSP9
IC2: BME680
JP1: HEADER-1X16_MIN; 1X16_ROUND_MIN
JP3: HEADER-1X12_MIN; 1X12_ROUND_MIN
LED1: WS2812B_SK6805_1515; SK6805_1515
Q1: BSS138; SOT23-R
Q3: DMG3415U; SOT23-R
R1, R2, R4, R5, R8, R10: 5.1K; 0603-NO
R3: 10K; RESPACK_4X0603
R7, R12: 100K; 0603-NO
R11: 22; 0603-NO
R17: 1Meg; 0603-NO
SW1, SW2: KMR2; BTN_KMR2_4.6X2.8
TP1: TESTPOINTROUND1.5MMNO; TESTPOINT_ROUND_1.5MM_NO
U2, U5: AP2112-3.3; SOT23-5
U3: MCP73831T-2ACI/OT; SOT23-5
U4: BME280
U6: ESP32-S3-MINI-1; QFN60_ESP32-S2-MINI-1_EXP; MANUFACTURER_PART_NUMBER ESP32-S2-MINI-1
U$31, U$32: MOUNTINGHOLE2.5; MOUNTINGHOLE_2.5_PLATED
U$34, U$35, U$55, U$56: FIDUCIAL_1MM
X1: JSTPH; JSTPH2_BATT
X3: USB C; USB_C_CUSB31-CFM2AX-01-X

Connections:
3.3V: C1.1, C2.1, C7.1, C8.1, C9.1, C10.1, DISP1.12 (LEDA), JP1.14, JP1.15, R1.2, U2.5 (OUT), U6.3 (3V3)
A0: JP1.12, U6.22 (IO18/DAC2)
A1: JP1.11, U6.21 (IO17/DAC1)
A2: JP1.10, U6.20 (IO16)
A3: JP1.9, U6.19 (IO15)
A4: JP1.8, U6.18 (IO14)
A5: JP1.7, U6.12 (IO8)
BACKLITE: Q1.1 (G), U6.41 (IO45_SPIV)
BOOT0: SW1.B (S), SW1.B' (S1), TP1.P$1, U6.4 (IO0_BOOT0)
D5: JP3.10, U6.9 (IO5)
D6: JP3.9, U6.10 (IO6)
D9: JP3.8, U6.13 (IO9)
D10: JP3.7, U6.14 (IO10)
D11: JP3.6, U6.15 (IO11)
D12: JP3.5, U6.16 (IO12)
D13: JP3.4, R10.1, U6.17 (IO13)
D+: U6.24 (IO20/D+), X3.A6 (D+), X3.B6 (D+)
D-: U6.23 (IO19/D-), X3.A7 (D-), X3.B7 (D-)
EN: JP3.2, R7.1, U2.3 (EN)
GND: C1.2, C2.2, C3.2, C4.2, C5.2, C6.2, C7.2, C8.2, C9.2, C10.2, C11.2, C12.2, CONN1.1 (GND), CONN1.MT1 (MT), CONN1.MT2 (MT), D3.C, DISP1.8 (GND), DISP1.13 (GND), IC1.A1 (VSS), IC1.B1 (TEST), IC2.1 (GND), IC2.7 (GND), JP1.13, LED1.4 (GND), Q1.2 (S), R3.3 (1), R3.4 (1), R3.5 (2), R4.1, R5.1, R8.1, R12.1, R17.1, SW1.A, SW1.A' (P1), SW2.A, SW2.A' (P1), U2.2 (GND), U3.2 (VSS), U4.1 (GND), U4.7 (GND), U5.2 (GND), U6.1 (GND), U6.2 (GND), U6.42 (GND), U6.43 (GND), U6.46 (GND), U6.47 (GND), U6.48 (GND), U6.49 (GND), U6.50 (GND), U6.51 (GND), U6.52 (GND), U6.53 (GND), U6.54 (GND), U6.55 (GND), U6.56 (GND), U6.57 (GND), U6.58 (GND), U6.59 (GND), U6.60 (GND), U6.61 (EXP), U6.62 (GND), U6.63 (GND), U6.64 (GND), U6.65 (GND), U6.66 (EXP), U6.67 (EXP), U6.68 (EXP), U6.69 (EXP), U6.70 (EXP), U6.71 (EXP), U6.72 (EXP), U6.73 (EXP), X1.1, X1.NC1, X1.NC2, X3.A1B12 (GND), X3.B1A12 (GND)
I2C_PWR: R3.6 (2), U5.3 (EN), U6.25 (IO21)
IO38_DBLTAP: C5.1, R17.2, U6.34 (IO38)
LEDK: DISP1.11 (LEDK), R11.1
MISO: JP1.4, U6.33 (IO37)
MOSI: DISP1.3 (DATA), JP1.5, U6.31 (IO35)
unnamed: CHG0.C, R2.1
unnamed: Q1.3 (D), R11.2
unnamed: R2.2, U3.1 (STAT)
unnamed: R4.2, U3.5 (PROG)
unnamed: D3.A, R10.2
unnamed: R8.2, X3.A5 (CC1)
unnamed: R5.2, X3.B5 (CC2)
NEOPIX: LED1.1 (DI), U6.28 (IO33)
NEOPIX_PWR: LED1.2 (VDD), U6.29 (IO34)
RESET: C4.1, JP1.16, R1.1, SW2.B (S), SW2.B' (S1), U6.45 (EN)
RX: JP1.3, U6.6 (IO2)
SCK: DISP1.4 (CLOCK), JP1.6, U6.32 (IO36)
SCL: CONN1.4 (SCL), IC1.C2 (SCL), IC2.4 (SCK), JP3.11, R3.8 (2), U4.4 (SCK), U6.37 (IO41/TDI)
SDA: CONN1.3 (SDA), IC1.C1 (SDA), IC2.3 (SDI), JP3.12, R3.7 (2), U4.3 (SDI), U6.38 (IO42/TMS)
TFT_CS: DISP1.7 (CS), U6.11 (IO7)
TFT_DC: DISP1.5 (RS/DC), U6.35 (IO39/TCK)
TFT_RST: DISP1.6 (RESET), U6.36 (IO40/TDO)
TX: JP1.2, U6.5 (IO1)
TXD0: JP1.1, U6.39 (TXD0)
VBAT: C3.1, IC1.A3 (VDD), JP3.1, Q3.3 (D), U3.3 (VBAT), X1.2
VBUS: CHG0.A, D4.A, JP3.3, Q3.1 (G), R12.2, U3.4 (VDD), X3.A4B9 (VBUS), X3.B4A9 (VBUS)
VHI: C6.1, D4.C, Q3.2 (S), R7.2, U2.1 (IN), U5.1 (IN)
VSENSOR: C11.1, C12.1, CONN1.2 (V+), DISP1.10 (VDD), IC2.2 (CSB), IC2.5 (SDO), IC2.6 (VDDIO), IC2.8 (VDD), R3.1, R3.2 (1), U4.2 (CSB), U4.5 (SDO), U4.6 (VDDIO), U4.8 (VDD), U5.5 (OUT)

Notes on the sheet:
LED
RESET
5.0K = 200mA
NEOPIXEL
LIPO MONITOR
POWER AND FILTERING
PSRAMCS
LIPO CHARGING

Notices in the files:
parts/oomp_project_github_sparkfun_ma_key_ma_key_makey_makey_current/data/original/kicad_file.kicad_sch:
Released under the Creative Commons
http://creativecommons.org/licenses/by-sa/3.0
parts/oomp_project_github_sparkfun_n_rf52840_breakout_mdbt50_q_nrf52840_breakout_mdbt50q_current/data/original/kicad_file.kicad_sch:
https://creativecommons.org/licenses/by-sa/4.0
parts and their libraries:
COPYRIGHT: Copyright (C) 2018 Accelerated Designs. All rights reserved
Released under the Creative Commons Attribution Share-Alike 4.0 License
